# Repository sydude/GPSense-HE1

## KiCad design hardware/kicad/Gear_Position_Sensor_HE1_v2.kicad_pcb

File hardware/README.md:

This project was predominantly designed in Fusion 360 but the current design files are now in Kicad. 
The Fusion files are the prior multi-sensor design that used the Arduino Nano R4 as a host board.

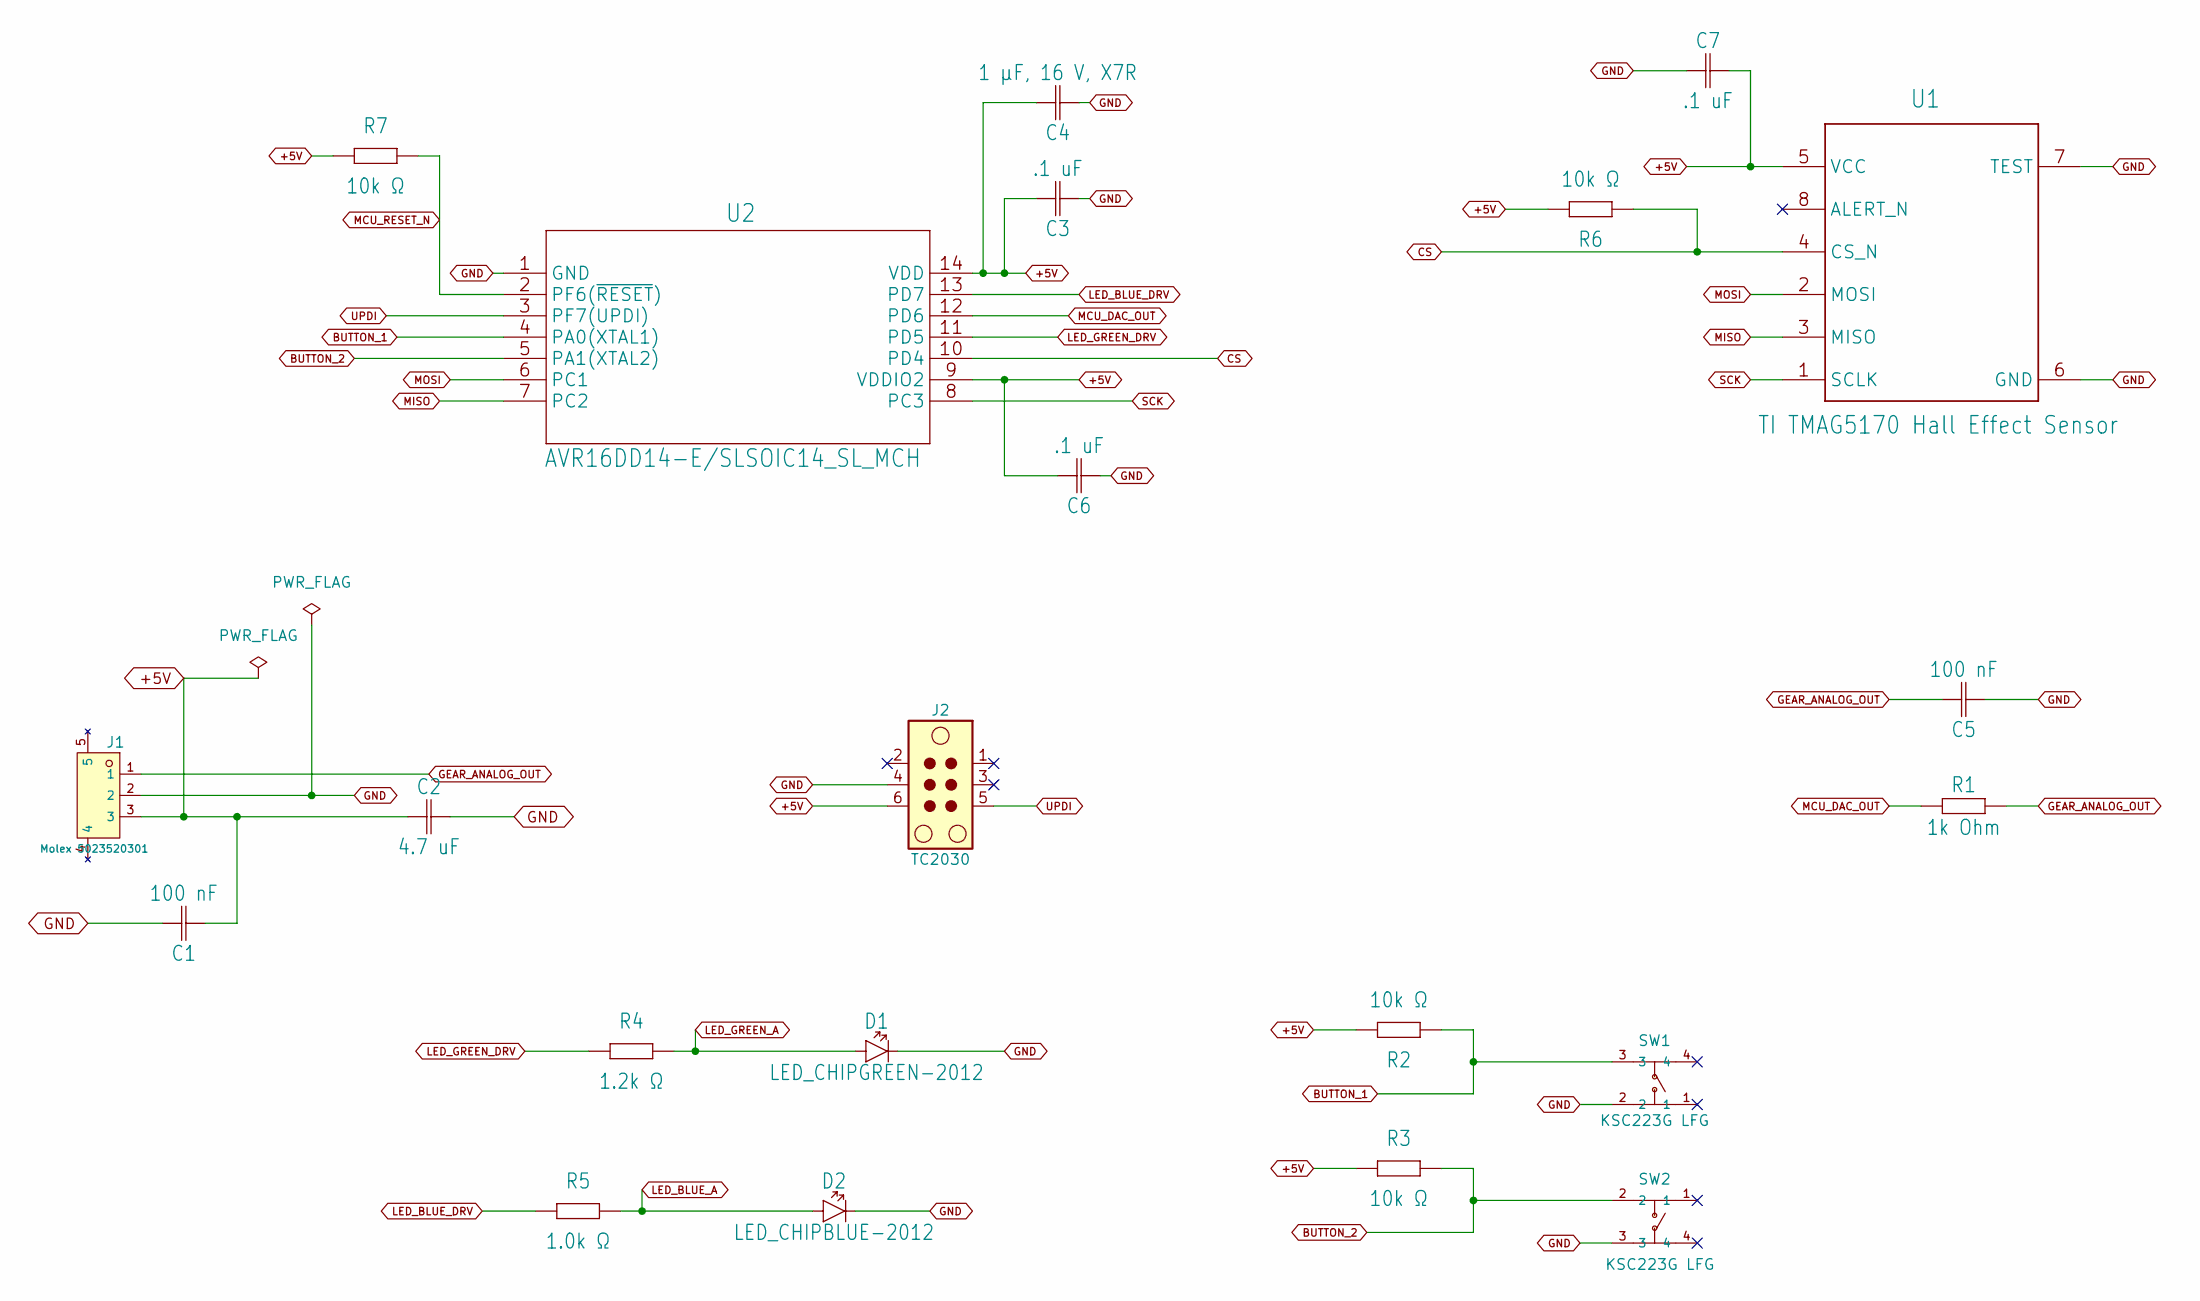
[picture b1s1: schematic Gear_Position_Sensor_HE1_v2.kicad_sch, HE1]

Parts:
C1, C5: 100 nF; CAPC1608X85; MPN KAF21BR71H104KM; LCSC C20213619
C2: 4.7 uF; CAPC1608X85; MPN 12065C475KAT2A; LCSC C141667
C3, C6, C7: .1 uF; CAPC1608X85; MPN KAF21BR71H104KM; LCSC C20213619
C4: 1 µF, 16 V, X7R; CAPC1608X85; MPN GCM188R71C105KA64D; LCSC C161212
D1: LED_CHIPGREEN-2012; LEDC2012X110N_G; MPN KT-0805G; LCSC C2297
D2: LED_CHIPBLUE-2012; LEDC2012X110N_G; MPN KT-0805B; LCSC C2293
J1: Molex 5023520301; C587901_CONN-TH_3P-P2_00_MOLEX_5023520301; MPN 5023520301; LCSC C587901
J2: TC2030; Tag-Connect_TC2030-IDC-FP_2x03_P1.27mm_Vertical
R1: 1k Ohm; RESC1608X60; MPN RC0603FR-071KL; LCSC C22548
R2, R3, R6, R7: 10k Ω; RESC1608X60; MPN RC0603FR-0710K; LCSC C98220
R4: 1.2k Ω; RESC1608X60; MPN RC0603FR-071K2L; LCSC C114605
R5: 1.0k Ω; RESC1608X60; MPN RC0603FR-071KL; LCSC C22548
SW1, SW2: KSC223G LFG; C2798957_KEY-SMD_4P-L6_2-W6_2-P4_00-LS10_0; MPN KSC223G LFG; LCSC C2798957
U1: TI TMAG5170 Hall Effect Sensor; DGK0008A-IPC_C; MANUFACTURER_PART_NUMBER TMAG5170A2QDGKR; LCSC C3716101
U2: AVR16DD14-E/SLSOIC14_SL_MCH; SOIC14_SL_MCH; MANUFACTURER_PART_NUMBER AVR16DD14-E/SL

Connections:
+5V: C1.1, C2.1, C3.2, C4.2, C6.2, C7.2, J1.3, J2.6, R2.2, R3.1, R6.2, R7.1, U1.5 (VCC), U2.9 (VDDIO2), U2.14 (VDD)
BUTTON_1: R2.1, SW1.3, U2.4 (PA0(XTAL1))
BUTTON_2: R3.2, SW2.2, U2.5 (PA1(XTAL2))
CS: R6.1, U1.4 (CS_N), U2.10 (PD4)
GEAR_ANALOG_OUT: C5.2, J1.1, R1.2
GND: C1.2, C2.2, C3.1, C4.1, C5.1, C6.1, C7.1, D1.1 (C), D2.1 (C), J1.2, J2.4, SW1.2, SW2.3, U1.6 (GND), U1.7 (TEST), U2.1 (GND)
LED_BLUE_A: D2.2 (A), R5.2
LED_BLUE_DRV: R5.1, U2.13 (PD7)
LED_GREEN_A: D1.2 (A), R4.2
LED_GREEN_DRV: R4.1, U2.11 (PD5)
MCU_DAC_OUT: R1.1, U2.12 (PD6)
MCU_RESET_N: R7.2, U2.2 (PF6(~RESET))
MISO: U1.3 (MISO), U2.7 (PC2)
MOSI: U1.2 (MOSI), U2.6 (PC1)
SCK: U1.1 (SCLK), U2.8 (PC3)
UPDI: J2.5, U2.3 (PF7(UPDI))

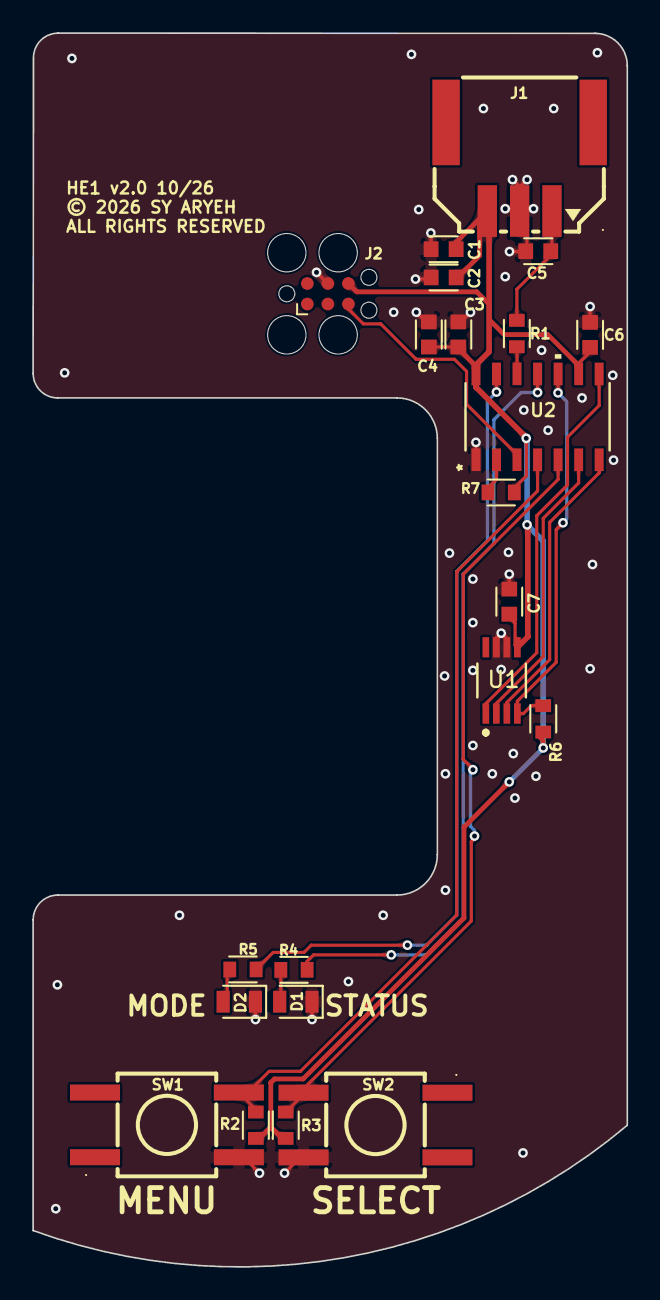
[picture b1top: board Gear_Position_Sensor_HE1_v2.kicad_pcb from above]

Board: 2 copper layers, 36.8 x 76.3 mm, 22 parts (0 on the bottom side), 16 nets.

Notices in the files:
hardware/kicad/Gear_Position_Sensor_HE1_v2.kicad_pcb:
© 2026 SY ARYEH
ALL RIGHTS RESERVED
parts and their libraries:
COPYRIGHT: Copyright (C) 2026 Ultra Librarian. All rights reserved.
